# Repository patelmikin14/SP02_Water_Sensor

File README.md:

**SP02 Sensor**

The first thing I did was get comfortable with the environment understanding the pre-installed component libraries, how symbols and power symbols work, and what a well-structured schematic actually looks like before touching the software. I reviewed the full circuit on paper first, mapped out all the requirements, and then rebuilt it from scratch in KiCad. Every connection, every component value, every net placed and verified manually. That foundation set the tone for everything that followed.

One habit I picked up early: run the Electrical Rules Check (ERC) frequently while building not just at the end. Catching errors right after adding a component is orders of magnitude faster than chasing them down in a finished schematic. I also got familiar with net labels and hierarchical mapping to keep the design clean and easy to reconfigure. Messy schematics are a silent time-killer.

The OLED module we planned to use wasn't in the KiCad library not even close. So, I built a custom symbol from scratch, mapping all the pins correctly, defining the data transfer pathways, and making sure it was compatible with the rest of the board architecture. Creating custom parts sounds intimidating at first, but it forces you to actually read and understand the datasheet rather than just trust a library entry someone else made.

Once the schematic was locked, every part needed a physical footprint the actual size and land pattern that lands on the board. Out of thousands of library options, I had to find the best match for each unique part, cross-referencing distributor availability, shipping feasibility, mechanical drawings, and datasheet dimensions. It was tedious. But this step is where a design moves from theoretically correct to actually manufacturable, and it's also where you can meaningfully optimize cost. Getting the balance right between quality, price, availability, and real-world workability is its own skill.

Two components both custom had no suitable footprint in the library. I used the KiCad footprint editor to build them out completely: pad definitions, through-hole geometry, courtyard, silkscreen labels, the works. Nothing about it was guesswork every dimension came from mechanical drawings and manufacturer specs.

Before placing a single trace, I picked the manufacturer and went through every single tolerance value they published minimum trace width, clearance, via drill size, copper weight and understood what each number actually meant for the design. Most experienced designers would pull these from a previous project. I went the long route on purpose. It made every constraint in the layout feel grounded in a real-world reason rather than an arbitrary rule.

Clearing the rat’s nest and turning a web of unconnected nets into clean, intentional traces is genuinely satisfying. I learned how vias fit into the routing strategy and why the type of connection matters as much as the connection itself particularly for designs that need to scale to higher-volume manufacturing. I also got into the layer stack up, understanding what each layer contributes and how they interact in the final physical board.

After routing, I added component designators, values, the board logo, and manufacturer markings then ran the Design Rules Check. DRC is the last line of defense before files leave your hands. It validates everything against the manufacturer's tolerances and catches the kind of errors that would be expensive or impossible to fix post-fabrication. If ERC is the schematic's safety net, DRC is the layouts. Both deserve real attention.

The final step was generating the Bill of Materials and Gerber files the package a manufacturer actually uses to build your board. Different manufacturers have different file format requirements, which is something worth checking before you start generating files. Once exported, the Gerbers can be uploaded directly to the manufacturer's portal to configure board specs, finish options, and quantities. Seeing the 3D render of the board after uploading is a good moment.

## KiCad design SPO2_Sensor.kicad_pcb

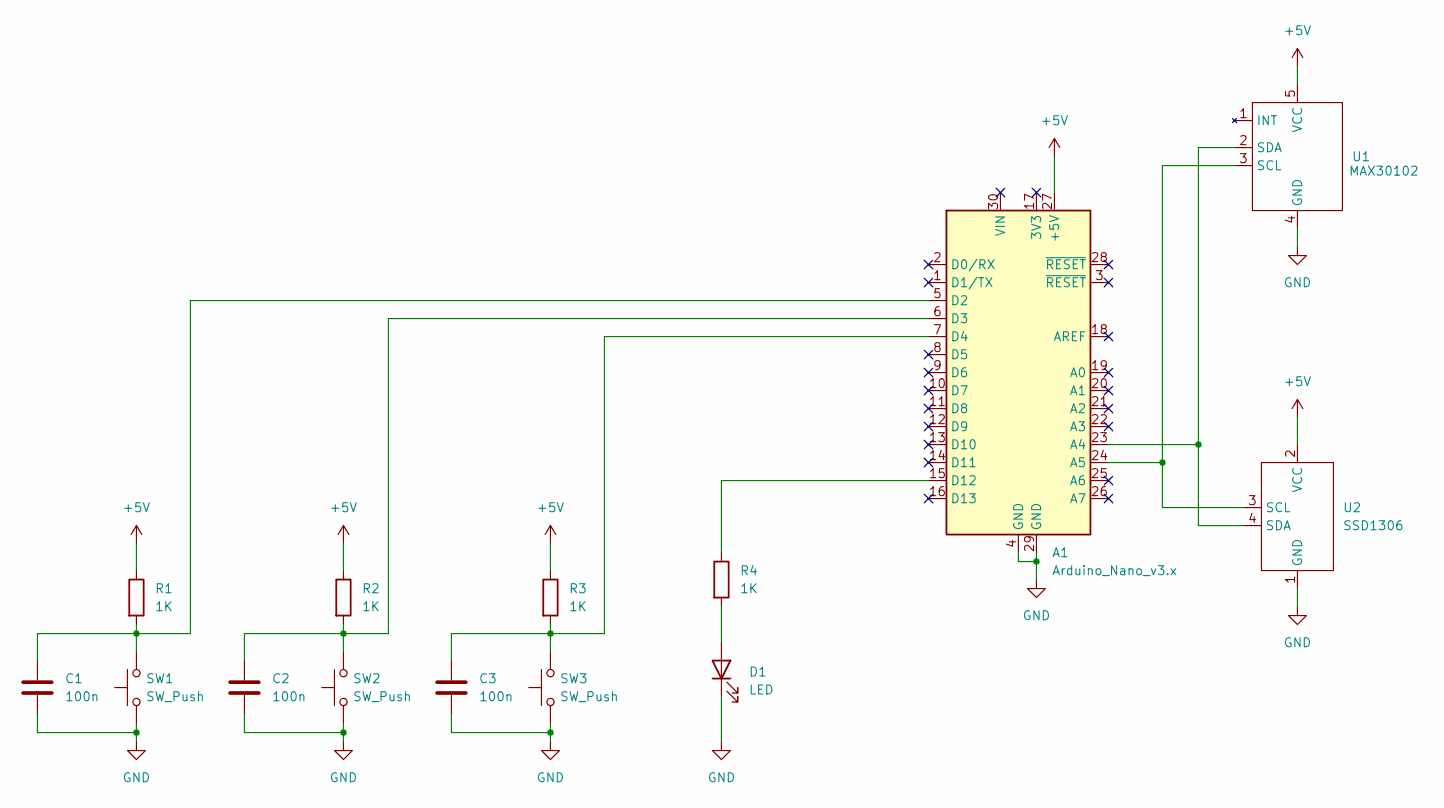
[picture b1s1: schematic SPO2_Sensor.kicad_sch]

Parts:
A1: Arduino_Nano_v3.x; Arduino_Nano
C1, C2, C3: 100n; C_Disc_D4.7mm_W2.5mm_P5.00mm
D1: LED; LED_D5.0mm
R1, R2, R3, R4: 1K; R_Axial_DIN0207_L6.3mm_D2.5mm_P7.62mm_Horizontal
SW1, SW2, SW3: SW_Push; SW_PUSH_6mm
U1: MAX30102; MAX30102_Module
U2: SSD1306

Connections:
+5V: A1.27 (+5V), R1.1, R2.1, R3.1, U1.5 (VCC), U2.2 (VCC)
GND: A1.4 (GND), A1.29 (GND), C1.2, C2.2, C3.2, D1.1 (K), SW1.1, SW2.1, SW3.1, U1.4 (GND), U2.1 (GND)
unnamed: A1.23 (A4), U1.2 (SDA), U2.4 (SDA)
unnamed: A1.24 (A5), U1.3 (SCL), U2.3 (SCL)
unnamed: A1.5 (D2), C1.1, R1.2, SW1.2
unnamed: A1.6 (D3), C2.1, R2.2, SW2.2
unnamed: A1.7 (D4), C3.1, R3.2, SW3.2
unnamed: A1.15 (D12), R4.1
unnamed: D1.2 (A), R4.2

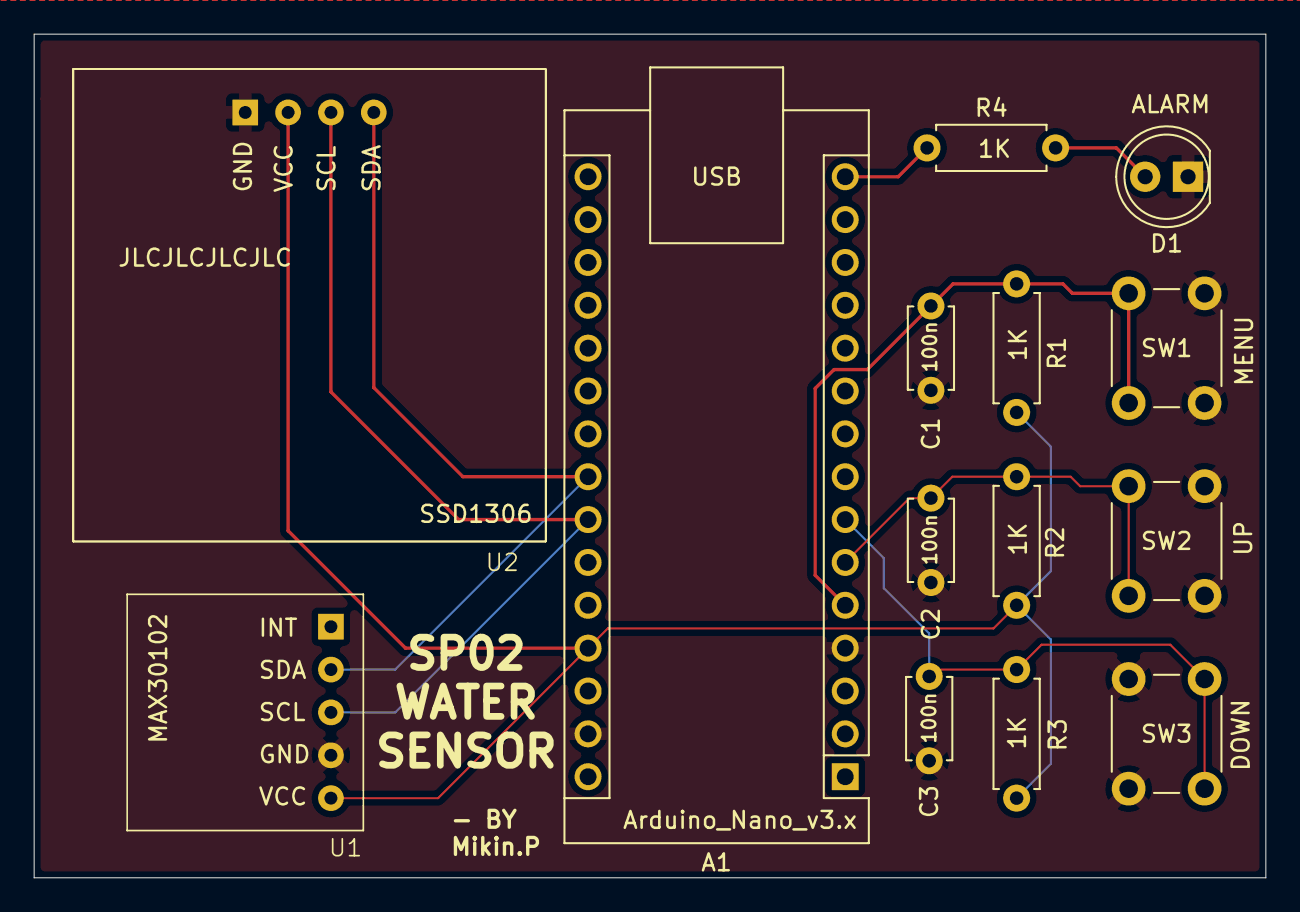
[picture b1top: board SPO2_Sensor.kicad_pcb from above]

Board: 2 copper layers, 73.0 x 50.0 mm, 14 parts (0 on the bottom side), 9 nets.
